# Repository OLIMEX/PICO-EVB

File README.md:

# PICO-EVB
Raspberry PICO/PICO-W evaluation board with optoisolated inputs 3.3-30VDC or 110-220VAC and Four Relays 15A/240VAC

https://www.olimex.com/Products/RaspberryPi/PICO/PICO-EVB/

## Licensee
* Hardware is released under CERN Open Hardware Licence Version 2 - Strongly Reciprocal
* Software is released under MIT Licensee
* Documentation is released under CC BY-SA 4.0

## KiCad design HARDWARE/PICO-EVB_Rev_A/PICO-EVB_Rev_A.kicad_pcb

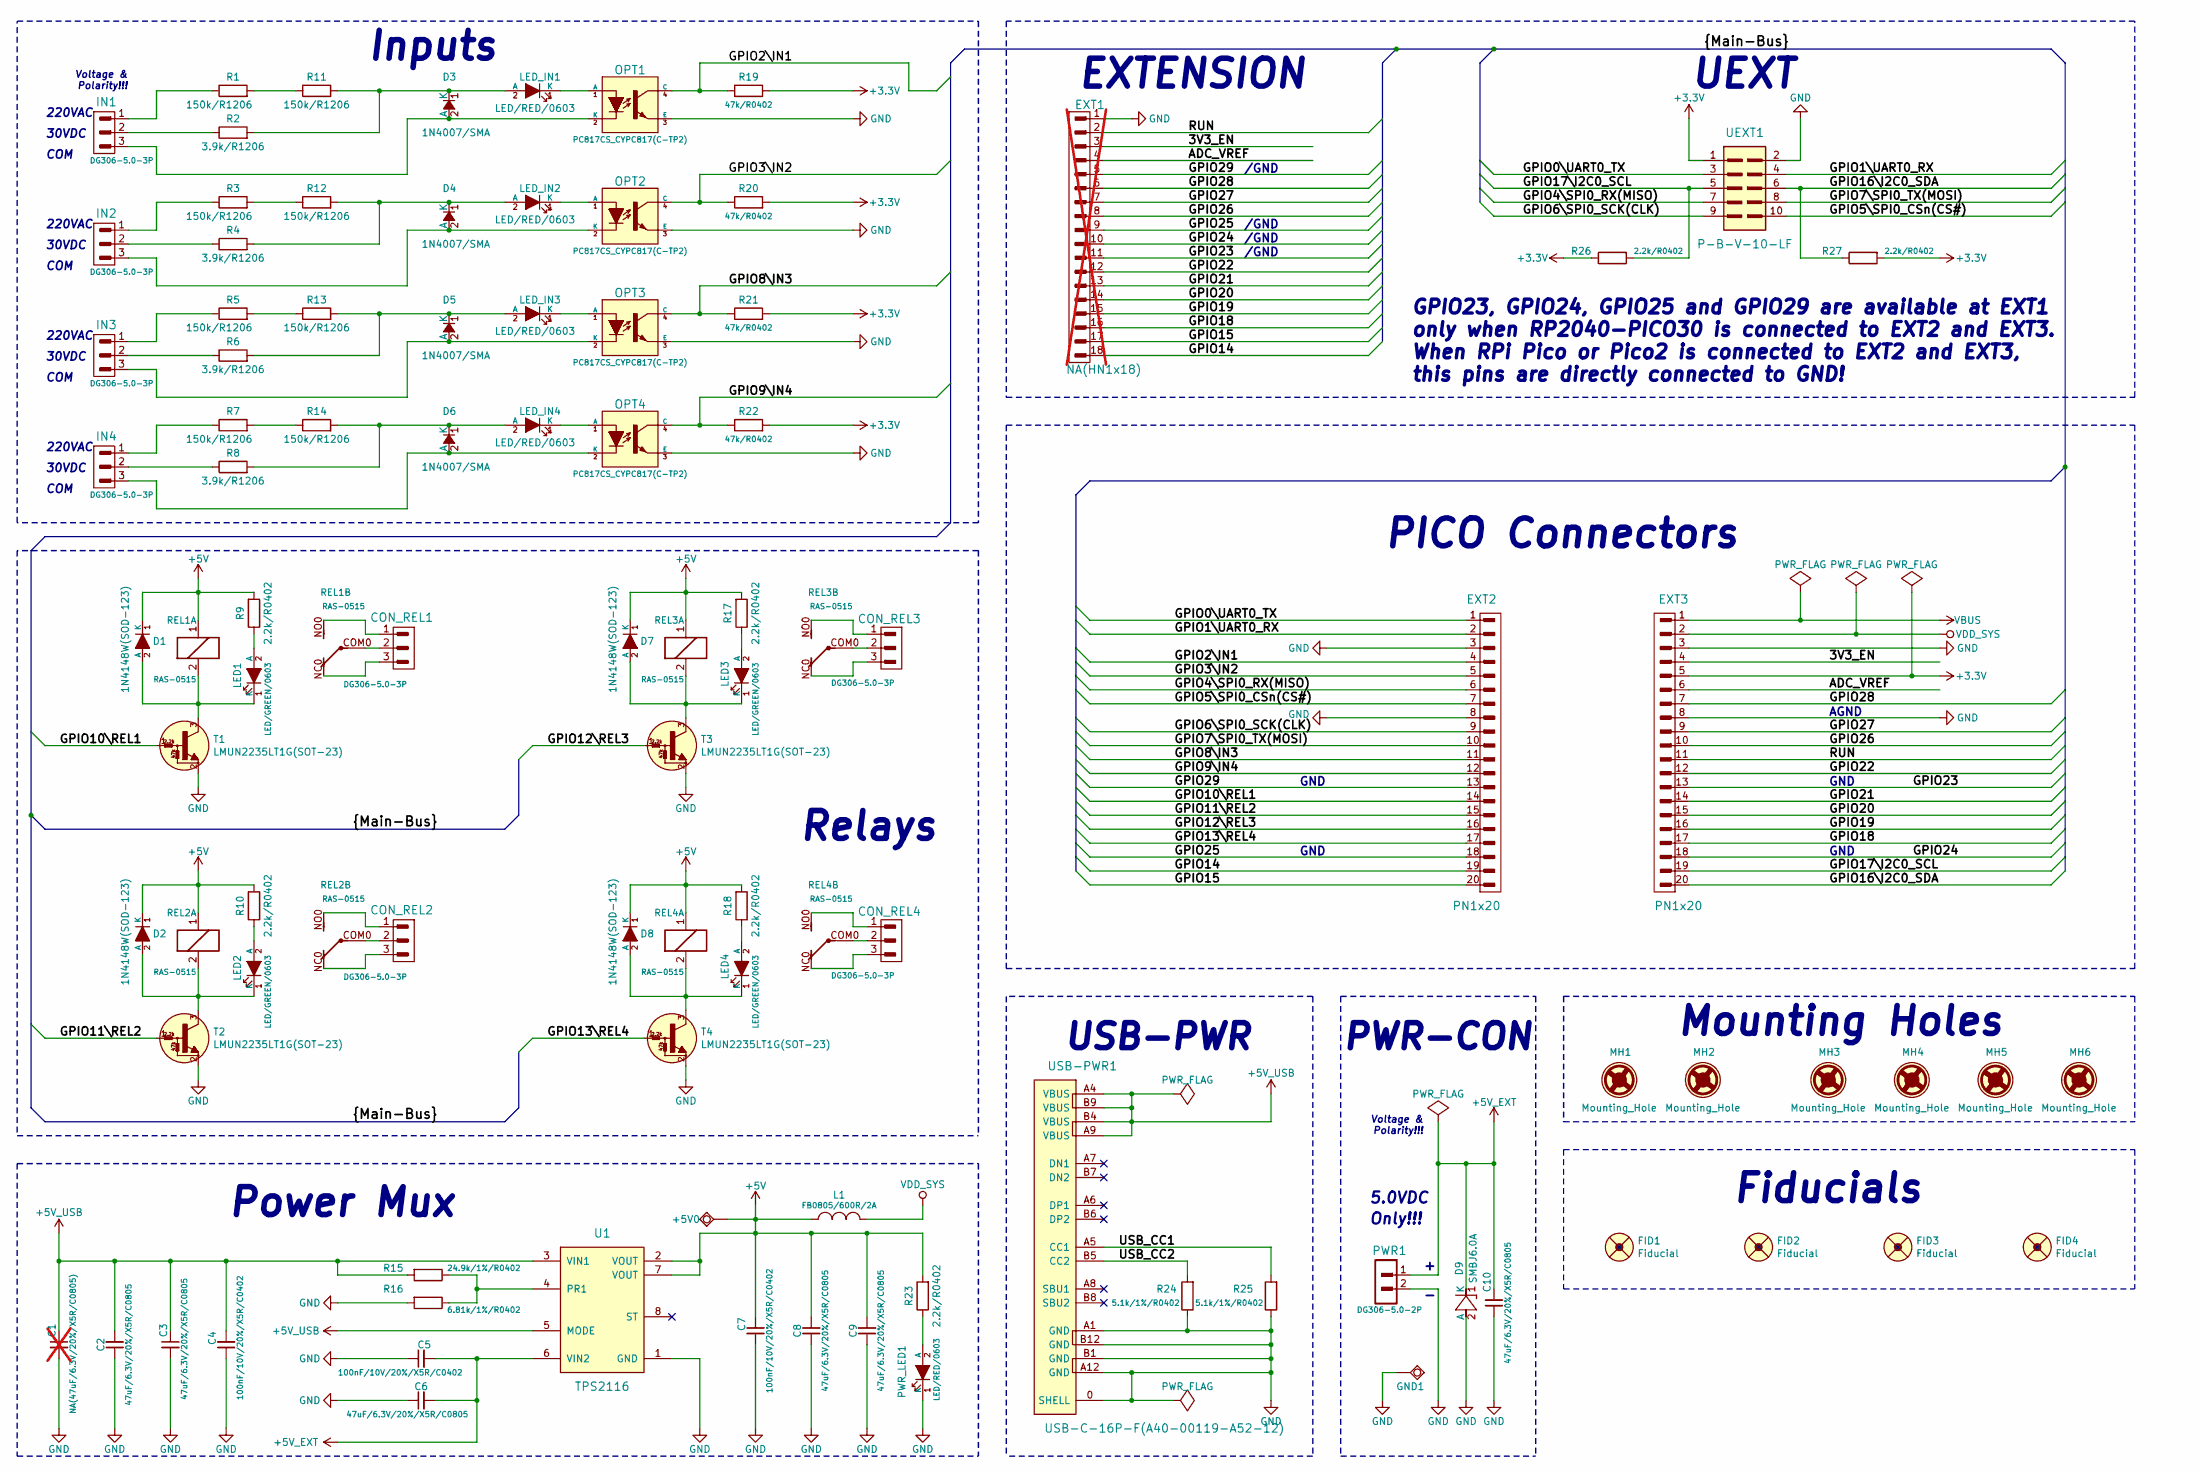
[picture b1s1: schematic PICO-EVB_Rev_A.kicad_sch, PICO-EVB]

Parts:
+5V0: TESTPAD; TEST_PAD40x70_SQUARE
C1: NA(47uF/6.3V/20%/X5R/C0805); C_0805_5MIL_DWS; not fitted
C2, C3, C6, C8, C9, C10: 47uF/6.3V/20%/X5R/C0805; C_0805_5MIL_DWS
C4, C5, C7: 100nF/10V/20%/X5R/C0402; C_0402_5MIL_DWS
CON_REL1, CON_REL2, CON_REL3, CON_REL4: DG306-5.0-3P; TB3-DG306-5.0_3P
D1, D2, D7, D8: 1N4148W(SOD-123); SOD-123_1C-2A_KA
D3, D4, D5, D6: 1N4007/SMA; SMA-KA
D9: SMBJ6.0A; DO214AA_1(K)-2(A)
EXT1: NA(HN1x18); HN1x18; not fitted
EXT2, EXT3: PN1x20
FID1, FID3: Fiducial; Fiducial1x3
FID2, FID4: Fiducial; Fiducial1x3_Paste
GND1: TESTPAD; TEST_PAD40x70_SQUARE
IN1, IN2, IN3, IN4: DG306-5.0-3P; TB3-DG306-5.0_3P
L1: FB0805/600R/2A; L_0805_5MIL_DWS
LED1, LED2, LED3, LED4: LED/GREEN/0603; LED_0603_KA
LED_IN1, LED_IN2, LED_IN3, LED_IN4: LED/RED/0603; LED_0603_KA
MH1, MH2: Mounting_Hole; Mounting_Hole_Drill-2.1mm_Clerance-4mm
MH3, MH4, MH5, MH6: Mounting_Hole; Mounting_Hole_Drill-3.3mm_Clerance-7mm
OPT1, OPT2, OPT3, OPT4: PC817CS_CYPC817(C-TP2); H11A817C_SMD(PC817X3NIP06)_FP
PWR1: DG306-5.0-2P; TB2-DG306-5.0_2P
PWR_LED1: LED/RED/0603; LED_0603_KA
R1, R3, R5, R7, R11, R12, R13, R14: 150k/R1206; R_1206_5MIL_DWS
R2, R4, R6, R8: 3.9k/R1206; R_1206_5MIL_DWS
R9, R10, R17, R18, R23, R26, R27: 2.2k/R0402; R_0402_5MIL_DWS
R15: 24.9k/1%/R0402; R_0402_5MIL_DWS
R16: 6.81k/1%/R0402; R_0402_5MIL_DWS
R19, R20, R21, R22: 47k/R0402; R_0402_5MIL_DWS
R24, R25: 5.1k/1%/R0402; R_0402_5MIL_DWS
REL1, REL2, REL3, REL4: RAS-0515; Relay_RAS-05-15
T1, T2, T3, T4: LMUN2235LT1G(SOT-23); SOT23
U1: TPS2116; SOT-5X3
UEXT1: P-B-V-10-LF; GBH-254-SMT-10
USB-PWR1: USB-C-16P-F(A40-00119-A52-12); USB2.0_TYPE-C(A40-00119-A52-12)_Paste

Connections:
+3.3V: EXT3.5, R19.2, R20.2, R21.2, R22.2, R26.1, R27.2, UEXT1.1
+5V: +5V0.1 (Pad), C7.2, C8.2, C9.2, D1.1 (K), D2.1 (K), D7.1 (K), D8.1 (K), L1.1, R9.2, R10.2, R17.2, R18.2, R23.2, REL1.1, REL2.1, REL3.1, REL4.1, U1.2 (VOUT), U1.7 (VOUT)
+5V_EXT: C5.2, C6.2, C10.2, D9.1 (K), PWR1.1, U1.6 (VIN2)
+5V_USB: C1.1, C2.2, C3.1, C4.2, R15.2, U1.3 (VIN1), U1.5 (MODE), USB-PWR1.A4 (VBUS), USB-PWR1.A9 (VBUS), USB-PWR1.B4 (VBUS), USB-PWR1.B9 (VBUS)
/3V3_EN: EXT1.3, EXT3.4
/ADC_VREF: EXT1.4, EXT3.6
/GPIO0\UART0_TX: EXT2.1, UEXT1.3
/GPIO1\UART0_RX: EXT2.2, UEXT1.4
/GPIO2\IN1: EXT2.4, OPT1.4 (C), R19.1
/GPIO3\IN2: EXT2.5, OPT2.4 (C), R20.1
/GPIO4\SPI0_RX(MISO): EXT2.6, UEXT1.7
/GPIO5\SPI0_CSn(CS#): EXT2.7, UEXT1.10
/GPIO6\SPI0_SCK(CLK): EXT2.9, UEXT1.9
/GPIO7\SPI0_TX(MOSI): EXT2.10, UEXT1.8
/GPIO8\IN3: EXT2.11, OPT3.4 (C), R21.1
/GPIO9\IN4: EXT2.12, OPT4.4 (C), R22.1
/GPIO10\REL1: EXT2.14, T1.1 (B)
/GPIO11\REL2: EXT2.15, T2.1 (B)
/GPIO12\REL3: EXT2.16, T3.1 (B)
/GPIO13\REL4: EXT2.17, T4.1 (B)
/GPIO14: EXT1.18, EXT2.19
/GPIO15: EXT1.17, EXT2.20
/GPIO16\I2C0_SDA: EXT3.20, R27.1, UEXT1.6
/GPIO17\I2C0_SCL: EXT3.19, R26.2, UEXT1.5
/GPIO18: EXT1.16, EXT3.17
/GPIO19: EXT1.15, EXT3.16
/GPIO20: EXT1.14, EXT3.15
/GPIO21: EXT1.13, EXT3.14
/GPIO22: EXT1.12, EXT3.12
/GPIO23: EXT1.11, EXT3.13
/GPIO24: EXT1.10, EXT3.18
/GPIO25: EXT1.9, EXT2.18
/GPIO26: EXT1.8, EXT3.10
/GPIO27: EXT1.7, EXT3.9
/GPIO28: EXT1.6, EXT3.7
/GPIO29: EXT1.5, EXT2.13
/RUN: EXT1.2, EXT3.11
/USB_CC1: R25.2, USB-PWR1.A5 (CC1)
/USB_CC2: R24.2, USB-PWR1.B5 (CC2)
GND: C1.2, C2.1, C3.2, C4.1, C5.1, C6.1, C7.1, C8.1, C9.1, C10.1, D9.2 (A), EXT1.1, EXT2.3, EXT2.8, EXT3.3, EXT3.8, GND1.1 (Pad), OPT1.3 (E), OPT2.3 (E), OPT3.3 (E), OPT4.3 (E), PWR1.2, PWR_LED1.1 (K), R16.2, R24.1, R25.1, T1.2 (E), T2.2 (E), T3.2 (E), T4.2 (E), U1.1 (GND), UEXT1.2, USB-PWR1.0 (SHELL), USB-PWR1.A1 (GND), USB-PWR1.A12 (GND), USB-PWR1.B1 (GND), USB-PWR1.B12 (GND)
unnamed: CON_REL1.1, REL1.NO0
unnamed: CON_REL1.2, REL1.COM0
unnamed: CON_REL1.3, REL1.NC0
unnamed: CON_REL2.1, REL2.NO0
unnamed: CON_REL2.2, REL2.COM0
unnamed: CON_REL2.3, REL2.NC0
unnamed: CON_REL3.1, REL3.NO0
unnamed: CON_REL3.2, REL3.COM0
unnamed: CON_REL3.3, REL3.NC0
unnamed: CON_REL4.1, REL4.NO0
unnamed: CON_REL4.2, REL4.COM0
unnamed: CON_REL4.3, REL4.NC0
unnamed: D1.2 (A), LED1.1 (K), REL1.2, T1.3 (C)
unnamed: D2.2 (A), LED2.1 (K), REL2.2, T2.3 (C)
unnamed: D3.2 (A), IN1.3, OPT1.2 (K)
unnamed: D3.1 (K), LED_IN1.2 (A), R2.2, R11.2
unnamed: D4.2 (A), IN2.3, OPT2.2 (K)
unnamed: D4.1 (K), LED_IN2.2 (A), R4.2, R12.2
unnamed: D5.2 (A), IN3.3, OPT3.2 (K)
unnamed: D5.1 (K), LED_IN3.2 (A), R6.2, R13.2
unnamed: D6.2 (A), IN4.3, OPT4.2 (K)
unnamed: D6.1 (K), LED_IN4.2 (A), R8.2, R14.2
unnamed: D7.2 (A), LED3.1 (K), REL3.2, T3.3 (C)
unnamed: D8.2 (A), LED4.1 (K), REL4.2, T4.3 (C)
unnamed: IN1.1, R1.1
unnamed: IN1.2, R2.1
unnamed: IN2.1, R3.1
unnamed: IN2.2, R4.1
unnamed: IN3.1, R5.1
unnamed: IN3.2, R6.1
unnamed: IN4.1, R7.1
unnamed: IN4.2, R8.1
unnamed: LED1.2 (A), R9.1
unnamed: LED2.2 (A), R10.1
unnamed: LED3.2 (A), R17.1
unnamed: LED4.2 (A), R18.1
unnamed: LED_IN1.1 (K), OPT1.1 (A)
unnamed: LED_IN2.1 (K), OPT2.1 (A)
unnamed: LED_IN3.1 (K), OPT3.1 (A)
unnamed: LED_IN4.1 (K), OPT4.1 (A)
unnamed: PWR_LED1.2 (A), R23.1
unnamed: R1.2, R11.1
unnamed: R3.2, R12.1
unnamed: R5.2, R13.1
unnamed: R7.2, R14.1
unnamed: R15.1, R16.1, U1.4 (PR1)
VBUS: EXT3.1
VDD_SYS: EXT3.2, L1.2

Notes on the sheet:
30VDC
PWR-CON
220VAC
/GND
AGND
Mounting Holes
USB-PWR
Fiducials
COM
Voltage & Polarity!!!
EXTENSION
GPIO23, GPIO24, GPIO25 and GPIO29 are available at EXT1 only when RP2040-PICO30 is connected to EXT2 and EXT3. When RPi Pico or Pico2 is connected to EXT2 and EXT3, this pins are directly connected to GND!
5.0VDC
Relays
Power Mux
UEXT
GND
Inputs
PICO Connectors
Only!!!

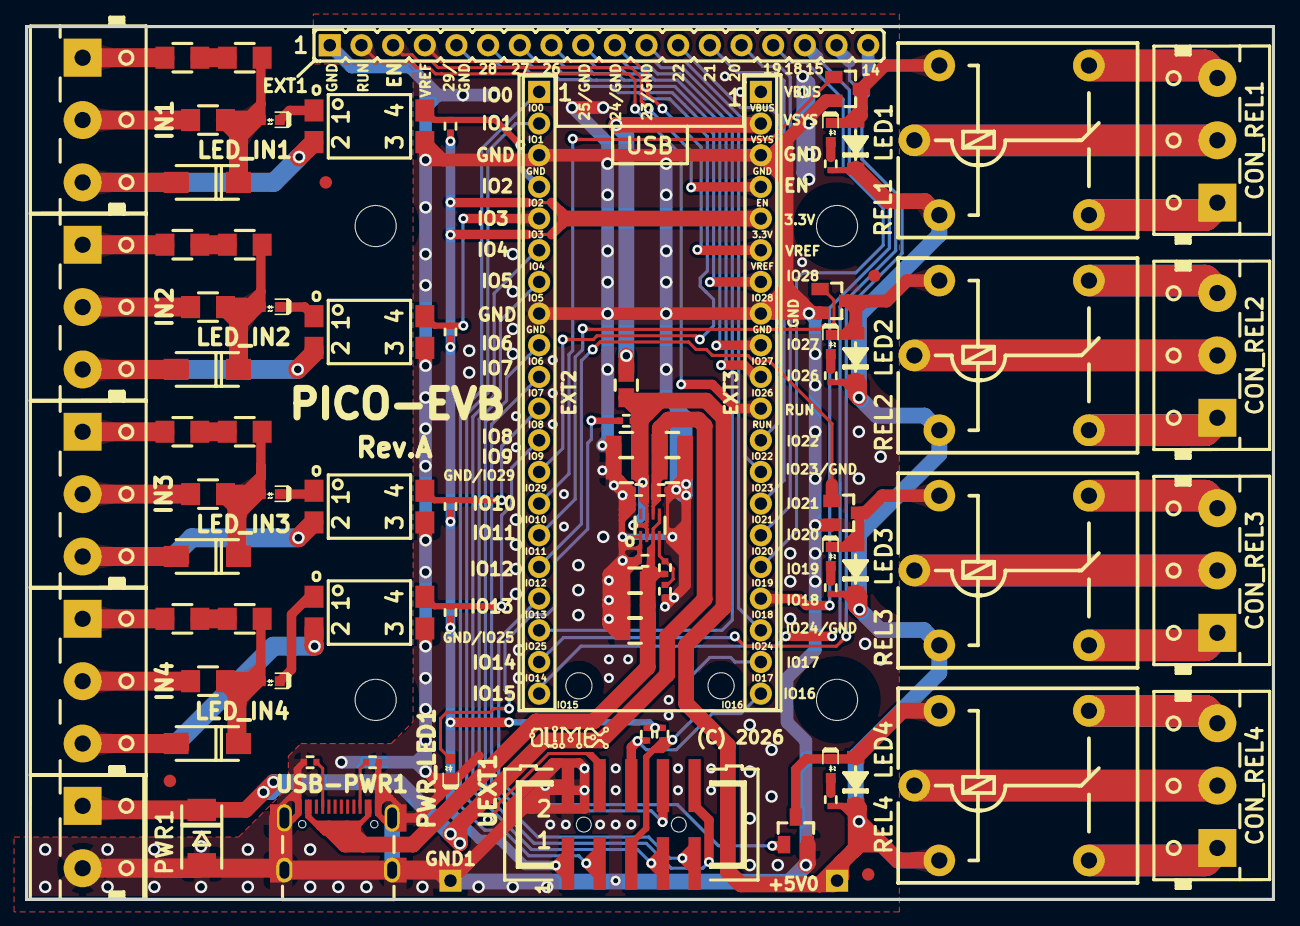
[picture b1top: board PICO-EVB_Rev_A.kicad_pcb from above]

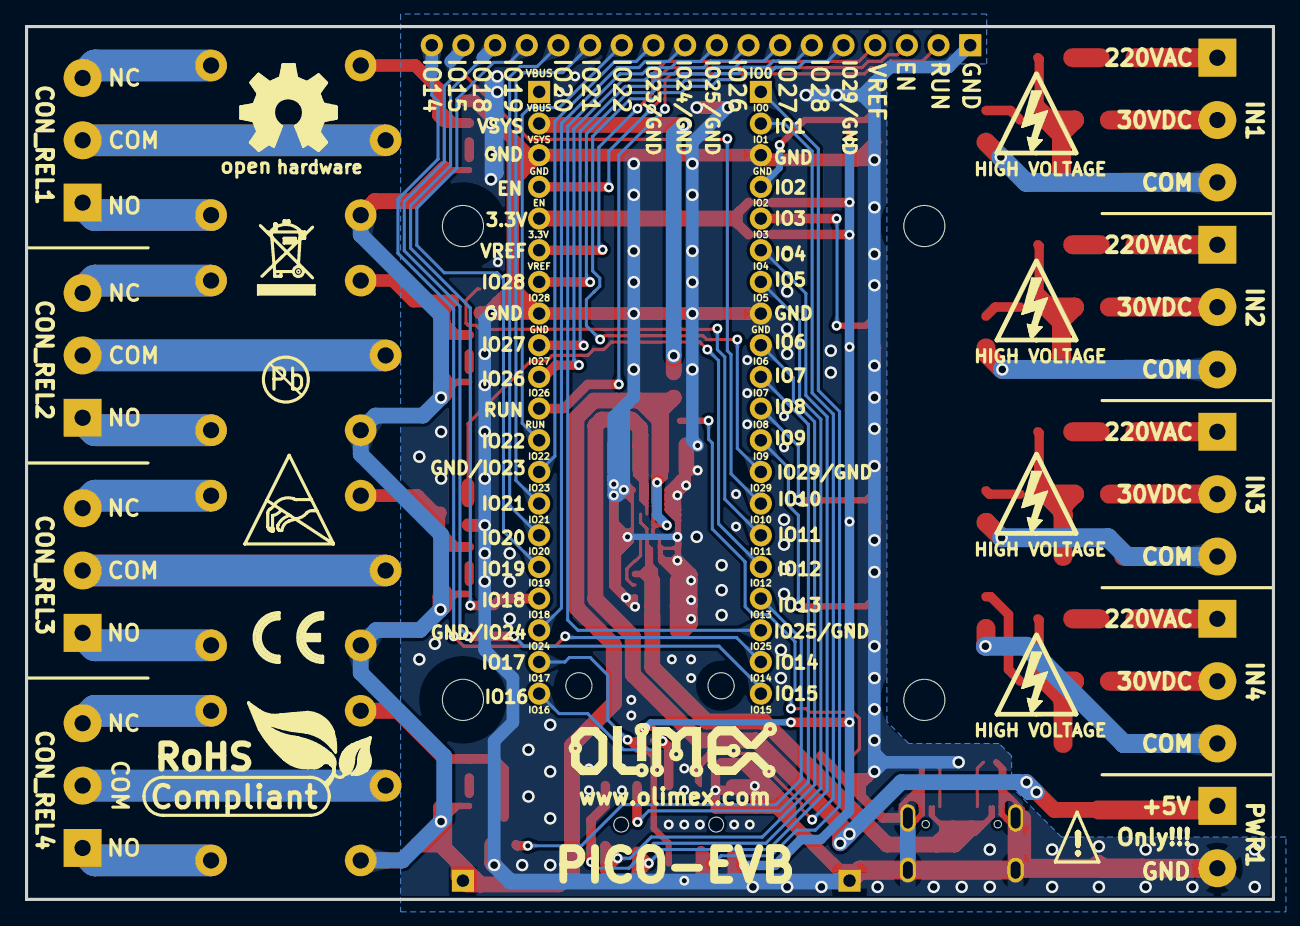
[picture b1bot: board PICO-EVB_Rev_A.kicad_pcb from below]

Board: 2 copper layers, 100.0 x 70.0 mm, 107 parts (11 on the bottom side), 87 nets.

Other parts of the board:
Logo_OLIMEX_SMALL_TB: Logo_OLIMEX_SMALL_TB
Logo_OLIMEX_TB: Logo_OLIMEX_TB
Sign_Antistatic: Sign_Antistatic
Sign_CE: CE_Sign
Sign_High_Voltage: Sign_High_Voltage
Sign_High_Voltage#2, Sign_High_Voltage#3, Sign_High_Voltage#4: Sign_High_Voltage
Sign_OSHW_8x8: Sign_OSHW_8x8
Sign_PB-Free: Sign_PB-Free
Sign_RecycleBin_1: Sign_RecycleBin_1
Sign_RoHS_1: Sign_RoHS_1

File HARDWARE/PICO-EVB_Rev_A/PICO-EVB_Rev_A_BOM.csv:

Quantity,Value,Footprint,Reference
6,47uF/6.3V/20%/X5R/C0805,C_0805_5MIL_DWS,"C2, C3, C6, C8, C9, C10"
3,100nF/10V/20%/X5R/C0402,C_0402_5MIL_DWS,"C4, C5, C7"
8,DG306-5.0-3P,TB3-DG306-5.0_3P,"CON_REL1, CON_REL2, CON_REL3, CON_REL4, IN1, IN2, IN3, IN4"
4,1N4148W(SOD-123),SOD-123_1C-2A_KA,"D1, D2, D7, D8"
4,1N4007/SMA,SMA-KA,"D3, D4, D5, D6"
1,SMBJ6.0A,DO214AA_1(K)-2(A),D9
2,PN1x20,PN1x20,"EXT2, EXT3"
1,FB0805/600R/2A,L_0805_5MIL_DWS,L1
4,LED/GREEN/0603,LED_0603_KA,"LED1, LED2, LED3, LED4"
5,LED/RED/0603,LED_0603_KA,"LED_IN1, LED_IN2, LED_IN3, LED_IN4, PWR_LED1"
4,PC817CS_CYPC817(C-TP2),H11A817C_SMD(PC817X3NIP06)_FP,"OPT1, OPT2, OPT3, OPT4"
1,DG306-5.0-2P,TB2-DG306-5.0_2P,PWR1
8,150k/R1206,R_1206_5MIL_DWS,"R1, R3, R5, R7, R11, R12, R13, R14"
4,3.9k/R1206,R_1206_5MIL_DWS,"R2, R4, R6, R8"
7,2.2k/R0402,R_0402_5MIL_DWS,"R9, R10, R17, R18, R23, R26, R27"
1,24.9k/1%/R0402,R_0402_5MIL_DWS,R15
1,6.81k/1%/R0402,R_0402_5MIL_DWS,R16
4,47k/R0402,R_0402_5MIL_DWS,"R19, R20, R21, R22"
2,5.1k/1%/R0402,R_0402_5MIL_DWS,"R24, R25"
4,RAS-0515,Relay_RAS-05-15,"REL1, REL2, REL3, REL4"
4,LMUN2235LT1G(SOT-23),SOT23,"T1, T2, T3, T4"
1,TPS2116,SOT-5X3,U1
1,P-B-V-10-LF,GBH-254-SMT-10,UEXT1
1,USB-C-16P-F(A40-00119-A52-12),USB2.0_TYPE-C(A40-00119-A52-12)_Paste,USB-PWR1

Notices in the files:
HARDWARE/PICO-EVB_Rev_A/PICO-EVB_Rev_A.kicad_pcb:
(C) 2026
